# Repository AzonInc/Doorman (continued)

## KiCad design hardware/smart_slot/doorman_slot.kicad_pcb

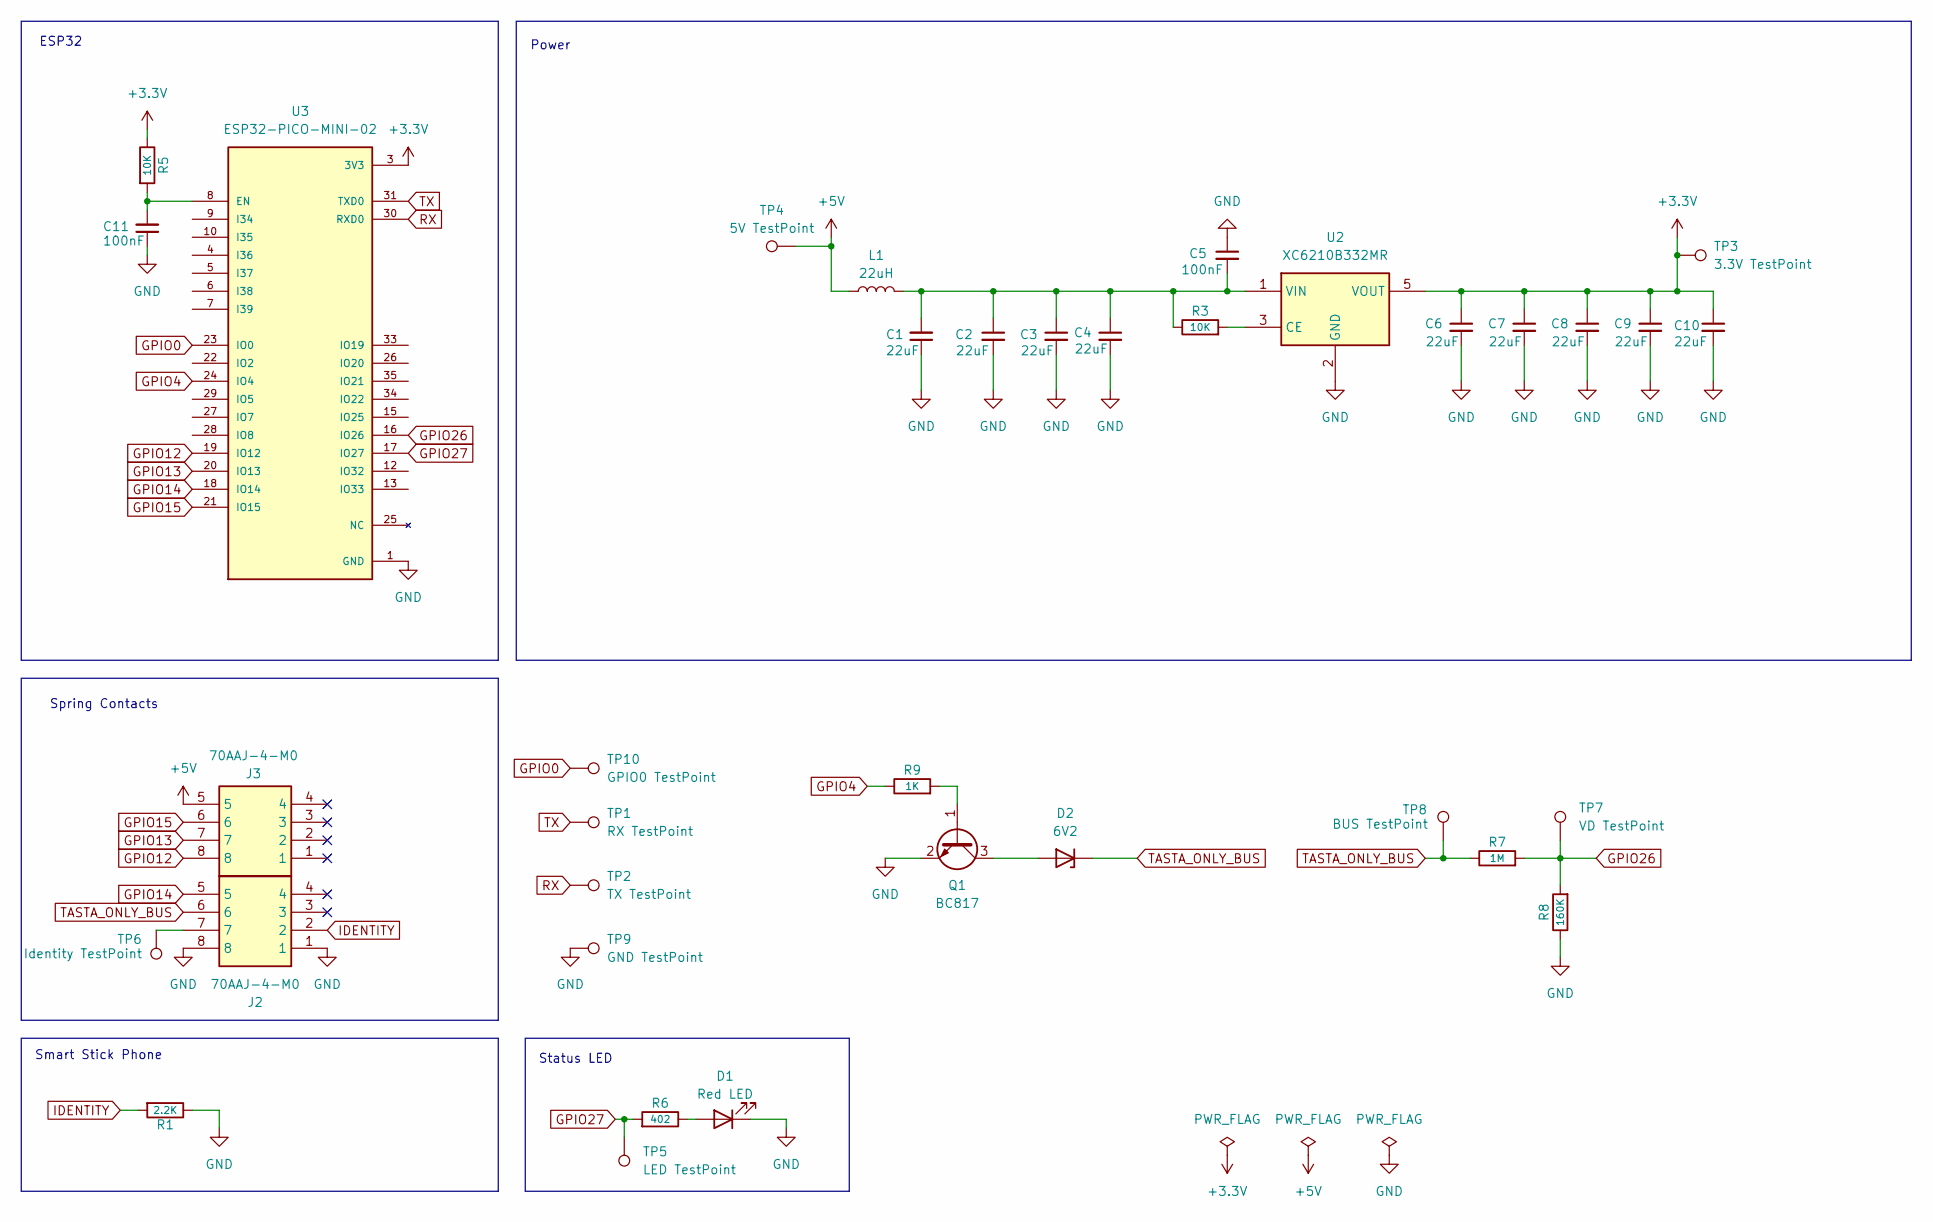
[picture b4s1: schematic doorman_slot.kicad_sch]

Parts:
C1, C2, C3, C4, C6, C7, C8, C9: 22uF; C_0603_1608Metric; LCSC C59461
C5, C11: 100nF; C_0402_1005Metric; LCSC C1525
C10: 22uF; C_0402_1005Metric; LCSC C105226
D1: Red LED; LED_0603_1608Metric
D2: 6V2; D_MiniMELF; MPN ZMM6B2; LCSC C3041470
J2, J3: 70AAJ-4-M0; 70AAJ4M0; Manufacturer_Part_Number 70AAJ-4-M0; Mouser Part Number 652-70AAJ-4-M0
L1: 22uH; L_APV_ANR4010; LCSC C83472
Q1: BC817; SOT-23; LCSC C5184412
R1: 2.2K; R_0402_1005Metric; LCSC C25879
R3, R5: 10K; R_0402_1005Metric; LCSC C25744
R6: 402; R_0402_1005Metric; LCSC C41042
R7: 1M; R_0603_1608Metric; LCSC C22935
R8: 160K; R_0603_1608Metric; LCSC C22813
R9: 1K; R_0402_1005Metric; LCSC C11702
TP1: RX TestPoint; TestPoint_Pad_D1.0mm
TP2: TX TestPoint; TestPoint_Pad_D1.0mm
TP3: 3.3V TestPoint; TestPoint_Pad_D1.0mm
TP4: 5V TestPoint; TestPoint_Pad_D1.0mm
TP5: LED TestPoint; TestPoint_Pad_D1.0mm
TP6: Identity TestPoint; TestPoint_Pad_D1.0mm
TP7: VD TestPoint; TestPoint_Pad_D1.0mm
TP8: BUS TestPoint; TestPoint_Pad_D1.0mm
TP9: GND TestPoint; TestPoint_Pad_D1.0mm
TP10: GPIO0 TestPoint; TestPoint_Pad_D1.0mm
U2: XC6210B332MR; SOT-23-5; LCSC C3021084
U3: ESP32-PICO-MINI-02; MODULE_ESP32-PICO-MINI-02; PARTREV v1.0; LCSC C2980306

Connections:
+3.3V: C6.1, C7.1, C8.1, C9.1, C10.1, R5.1, TP3.1, U2.5 (VOUT), U3.3 (3V3)
+5V: J3.5, L1.1, TP4.1
GND: C1.1, C2.2, C3.2, C4.2, C5.1, C6.2, C7.2, C8.2, C9.2, C10.2, C11.1, D1.1 (K), J2.1, J2.8, Q1.2 (E), R1.1, R8.1, TP9.1, U2.2 (GND), U3.1 (GND), U3.2 (GND), U3.11 (GND), U3.14 (GND), U3.36 (GND), U3.37 (GND), U3.38 (GND), U3.39 (GND), U3.40 (GND), U3.41 (GND), U3.42 (GND), U3.43 (GND), U3.44 (GND), U3.45 (GND), U3.46 (GND), U3.47 (GND), U3.48 (GND), U3.49 (GND), U3.50 (GND), U3.51 (GND), U3.52 (GND), U3.53 (GND), U3.54 (GND), U3.55 (GND), U3.56 (GND), U3.57 (GND), U3.58 (GND), U3.59 (GND), U3.60 (GND), U3.61 (GND)
GPIO0: TP10.1, U3.23 (IO0)
GPIO4: R9.1, U3.24 (IO4)
GPIO12: J3.8, U3.19 (IO12)
GPIO13: J3.7, U3.20 (IO13)
GPIO14: J2.5, U3.18 (IO14)
GPIO15: J3.6, U3.21 (IO15)
GPIO26: R7.2, R8.2, TP7.1, U3.16 (IO26)
GPIO27: R6.2, TP5.1, U3.17 (IO27)
IDENTITY: J2.2, R1.2
unnamed: D1.2 (A), R6.1
unnamed: D2.2 (A), Q1.3 (C)
unnamed: J2.7, TP6.1
unnamed: Q1.1 (B), R9.2
unnamed: R3.2, U2.3 (CE)
unnamed: C1.2, C2.1, C3.1, C4.1, C5.2, L1.2, R3.1, U2.1 (VIN)
unnamed: C11.2, R5.2, U3.8 (EN)
RX: TP2.1, U3.30 (RXD0)
TASTA_ONLY_BUS: D2.1 (K), J2.6, R7.1, TP8.1
TX: TP1.1, U3.31 (TXD0)

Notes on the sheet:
Spring Contacts
ESP32
Smart Stick Phone
Status LED
Power

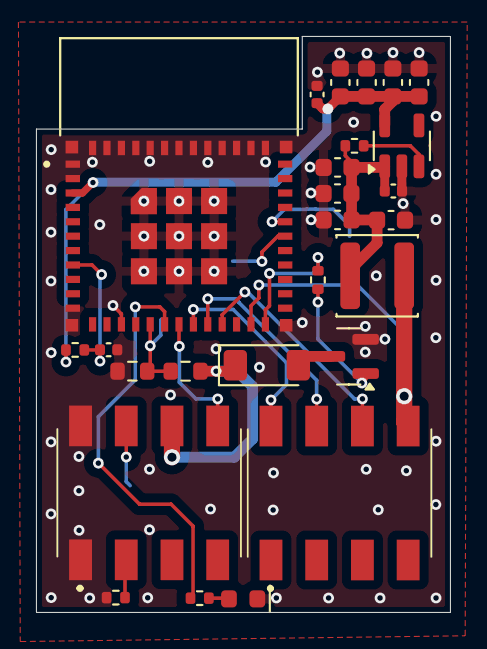
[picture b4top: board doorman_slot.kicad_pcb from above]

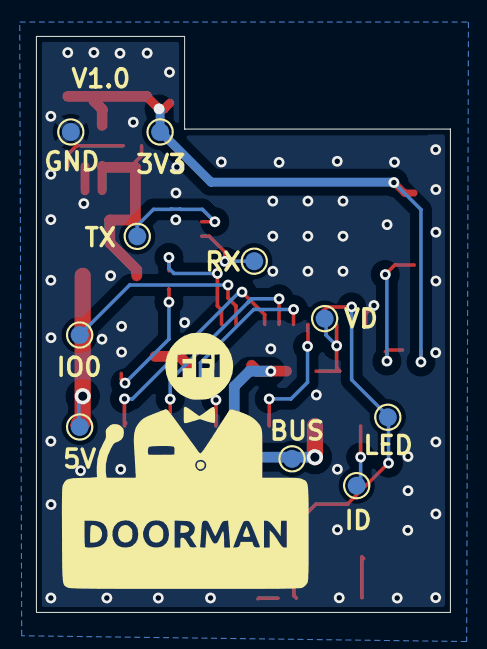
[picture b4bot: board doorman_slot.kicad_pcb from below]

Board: 4 copper layers, 23.0 x 32.0 mm, 36 parts (10 on the bottom side), 22 nets.

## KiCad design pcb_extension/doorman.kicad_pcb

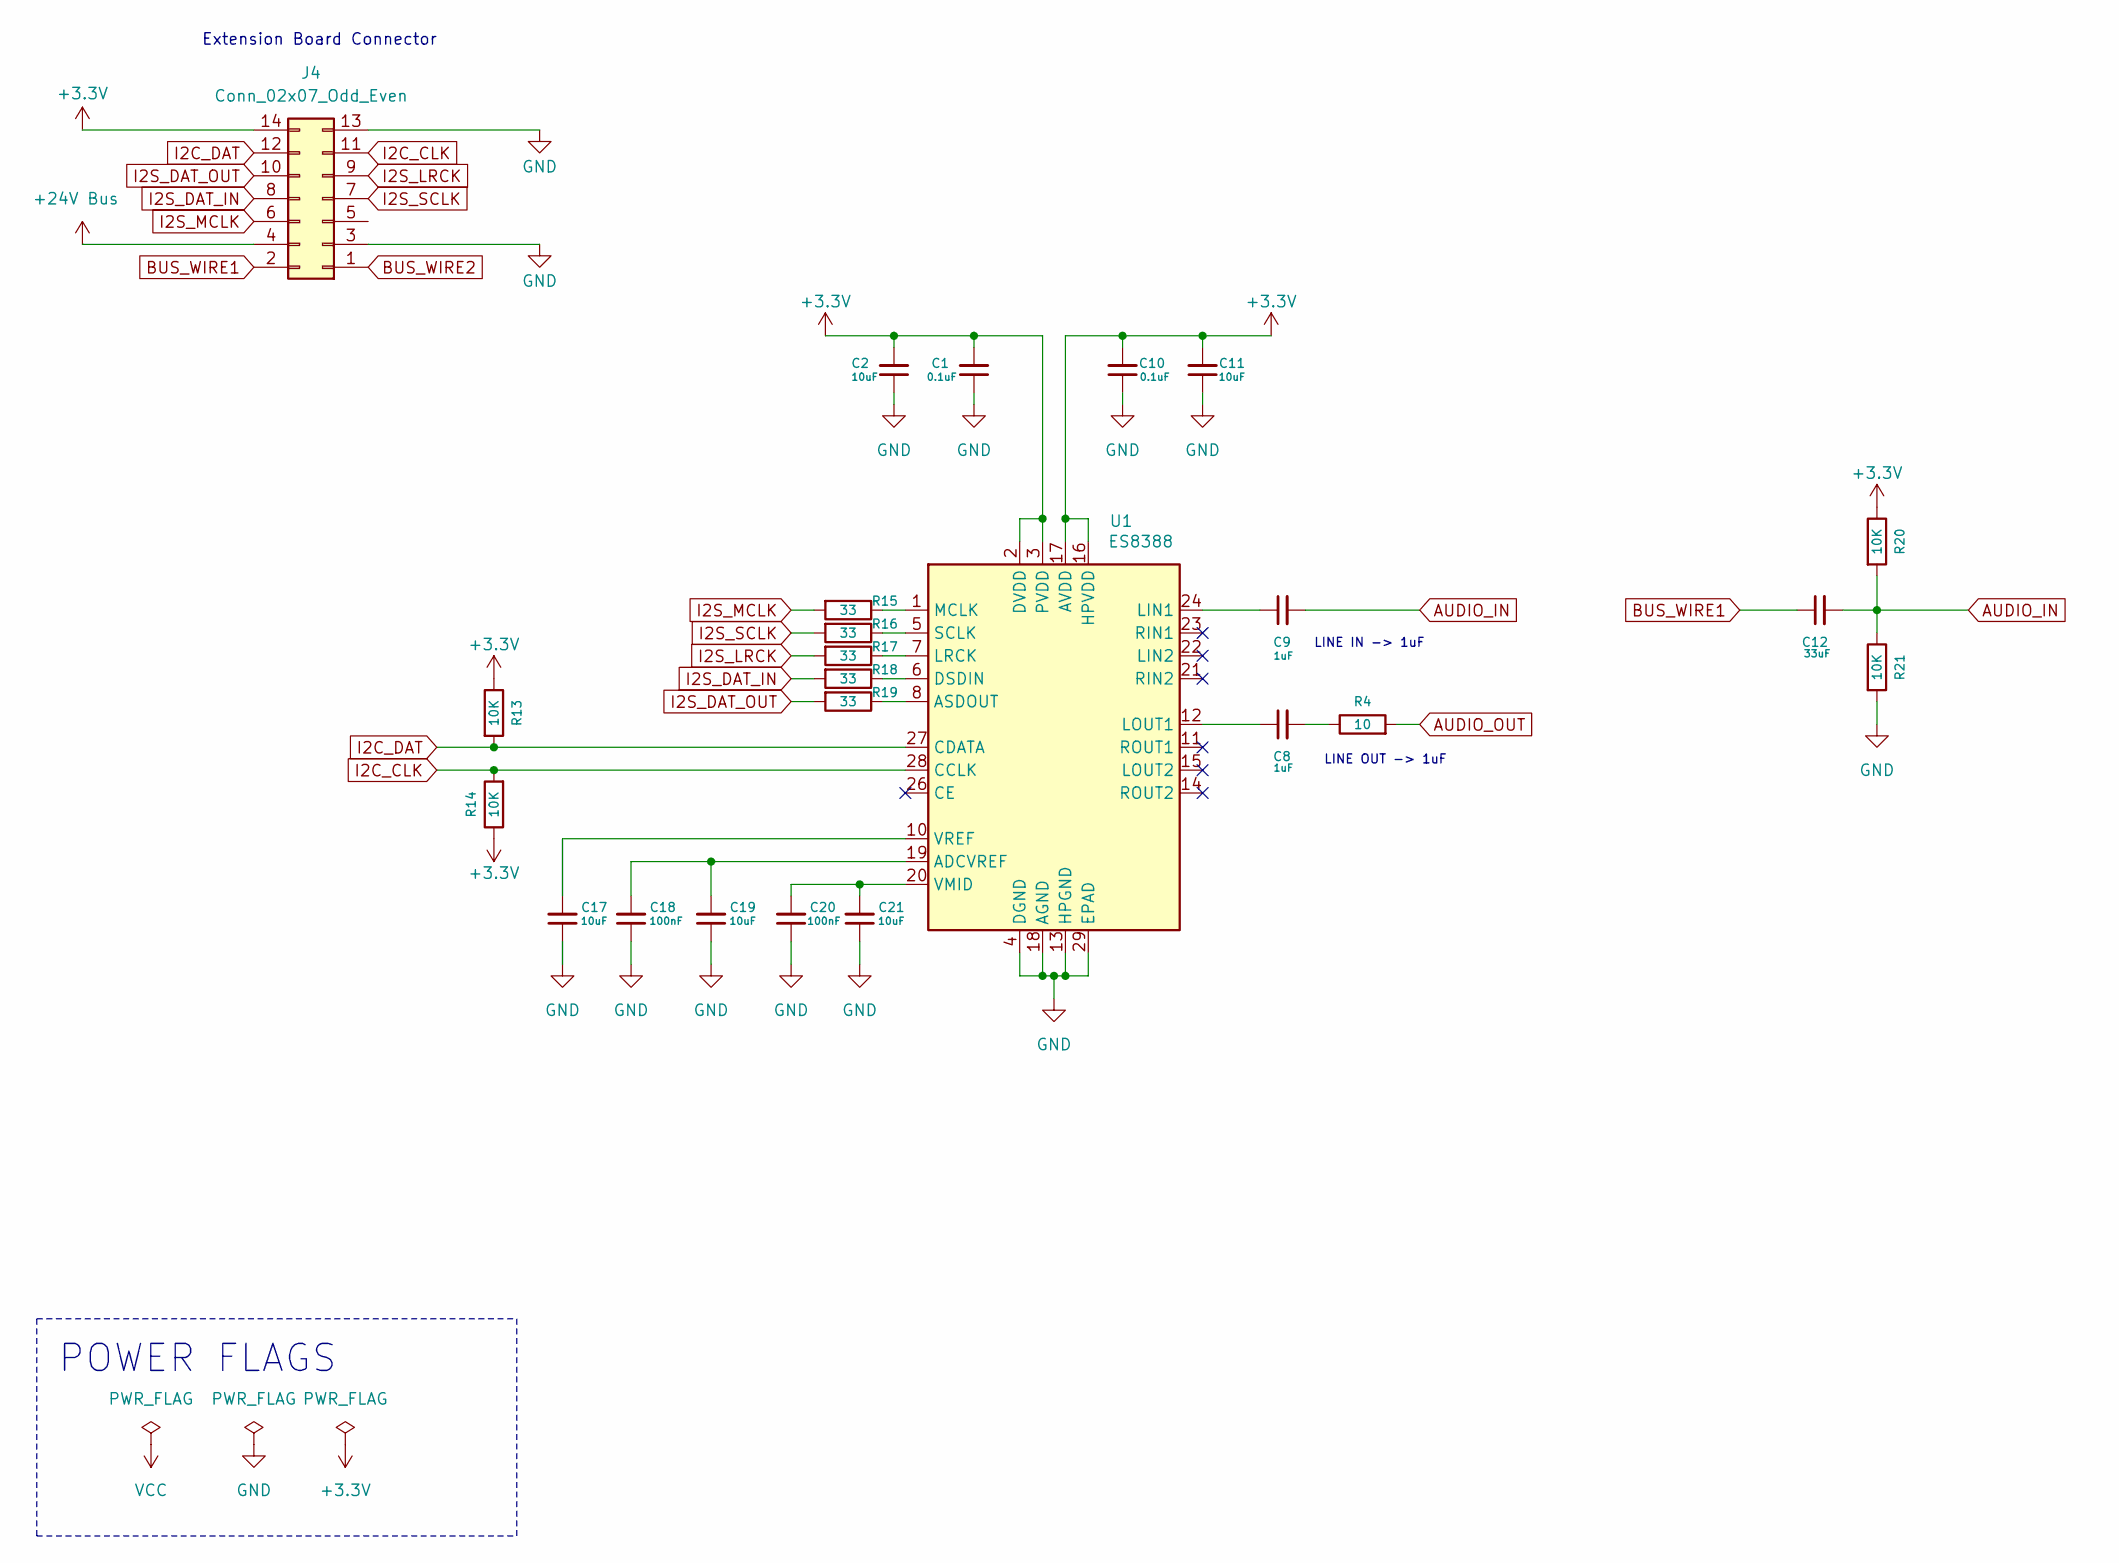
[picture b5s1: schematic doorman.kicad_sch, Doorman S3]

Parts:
C1, C10: 0.1uF; C_0603_1608Metric; MPN CC0603KRX7R9BB104; LCSC C14663
C2, C11, C17, C19, C21: 10uF; C_0603_1608Metric; MPN CC0603KRX7R9BB104; LCSC C14663
C8, C9: 1uF; C_0603_1608Metric; MPN CC0603KRX7R9BB104; LCSC C14663
C12: 33uF; C_1206_3216Metric; MPN CC0603KRX7R9BB104; LCSC C14663
C18, C20: 100nF; C_0603_1608Metric; MPN CC0603KRX7R9BB104; LCSC C14663
J4: Conn_02x07_Odd_Even; PinHeader_2x07_P2.00mm_Vertical_SMD; MPN PM200-2-07-S-4.3; LCSC C3975171
R4: 10; R_0402_1005Metric; MPN 0402WGF5101TCE; LCSC C25905
R13, R14: 10K; R_0402_1005Metric; MPN 0402WGF5101TCE; LCSC C25905
R15, R16, R17, R18, R19: 33; R_0402_1005Metric; MPN 0402WGF5101TCE; LCSC C25905
R20, R21: 10K; R_0603_1608Metric; MPN 0402WGF5101TCE; LCSC C25905
U1: ES8388; QFN-28-1EP_4x4mm_P0.45mm_EP2.6x2.6mm

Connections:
+3.3V: C1.2, C2.2, C10.2, C11.2, J4.14, R13.1, R14.1, R20.1, U1.2 (DVDD), U1.3 (PVDD), U1.16 (HPVDD), U1.17 (AVDD)
+24V Bus: J4.4
AUDIO_IN: C9.2, C12.2, R20.2, R21.1
AUDIO_OUT: R4.2
BUS_WIRE1: C12.1, J4.2
BUS_WIRE2: J4.1
GND: C1.1, C2.1, C10.1, C11.1, C17.1, C18.1, C19.1, C20.1, C21.1, J4.3, J4.13, R21.2, U1.4 (DGND), U1.13 (HPGND), U1.18 (AGND), U1.29 (EPAD)
I2C_CLK: J4.11, R14.2, U1.28 (CCLK)
I2C_DAT: J4.12, R13.2, U1.27 (CDATA)
I2S_DAT_IN: J4.8, R18.2
I2S_DAT_OUT: J4.10, R19.2
I2S_LRCK: J4.9, R17.2
I2S_MCLK: J4.6, R15.2
I2S_SCLK: J4.7, R16.2
unnamed: C8.2, R4.1
unnamed: C18.2, C19.2, U1.19 (ADCVREF)
unnamed: R19.1, U1.8 (ASDOUT)
unnamed: R18.1, U1.6 (DSDIN)
unnamed: C9.1, U1.24 (LIN1)
unnamed: C8.1, U1.12 (LOUT1)
unnamed: R17.1, U1.7 (LRCK)
unnamed: R15.1, U1.1 (MCLK)
unnamed: R16.1, U1.5 (SCLK)
unnamed: C20.2, C21.2, U1.20 (VMID)
unnamed: C17.2, U1.10 (VREF)

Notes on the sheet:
LINE OUT -> 1uF
LINE IN -> 1uF
Extension Board Connector
POWER FLAGS

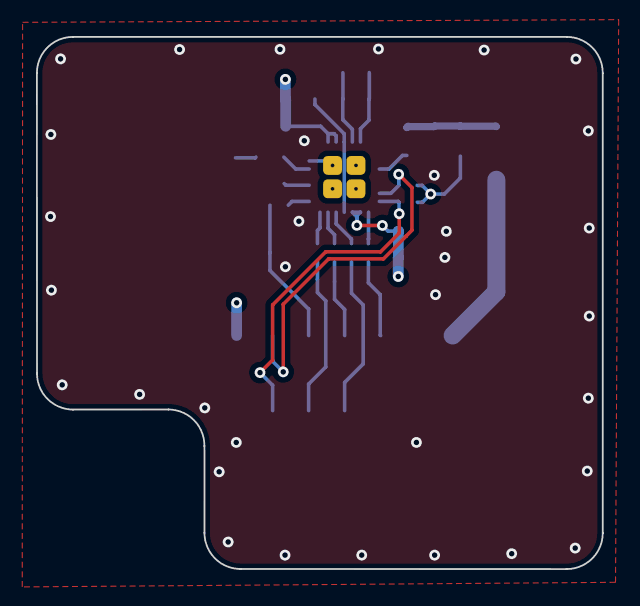
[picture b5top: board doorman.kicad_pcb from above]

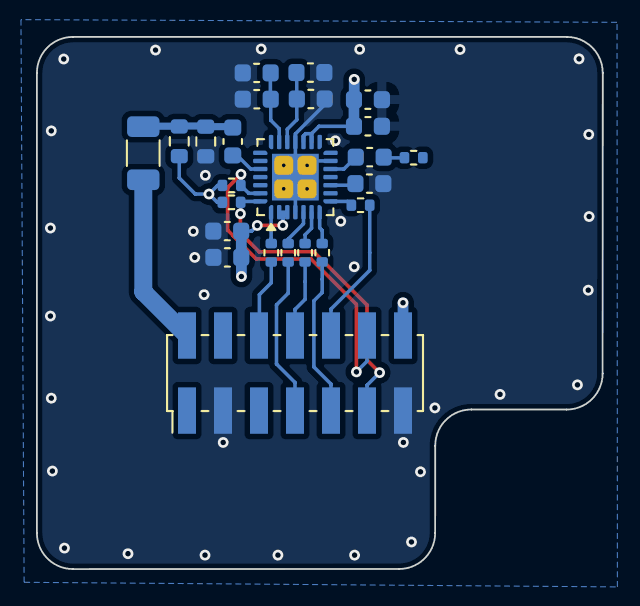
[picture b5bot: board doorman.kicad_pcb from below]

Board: 4 copper layers, 31.4 x 29.6 mm, 24 parts (24 on the bottom side), 22 nets.

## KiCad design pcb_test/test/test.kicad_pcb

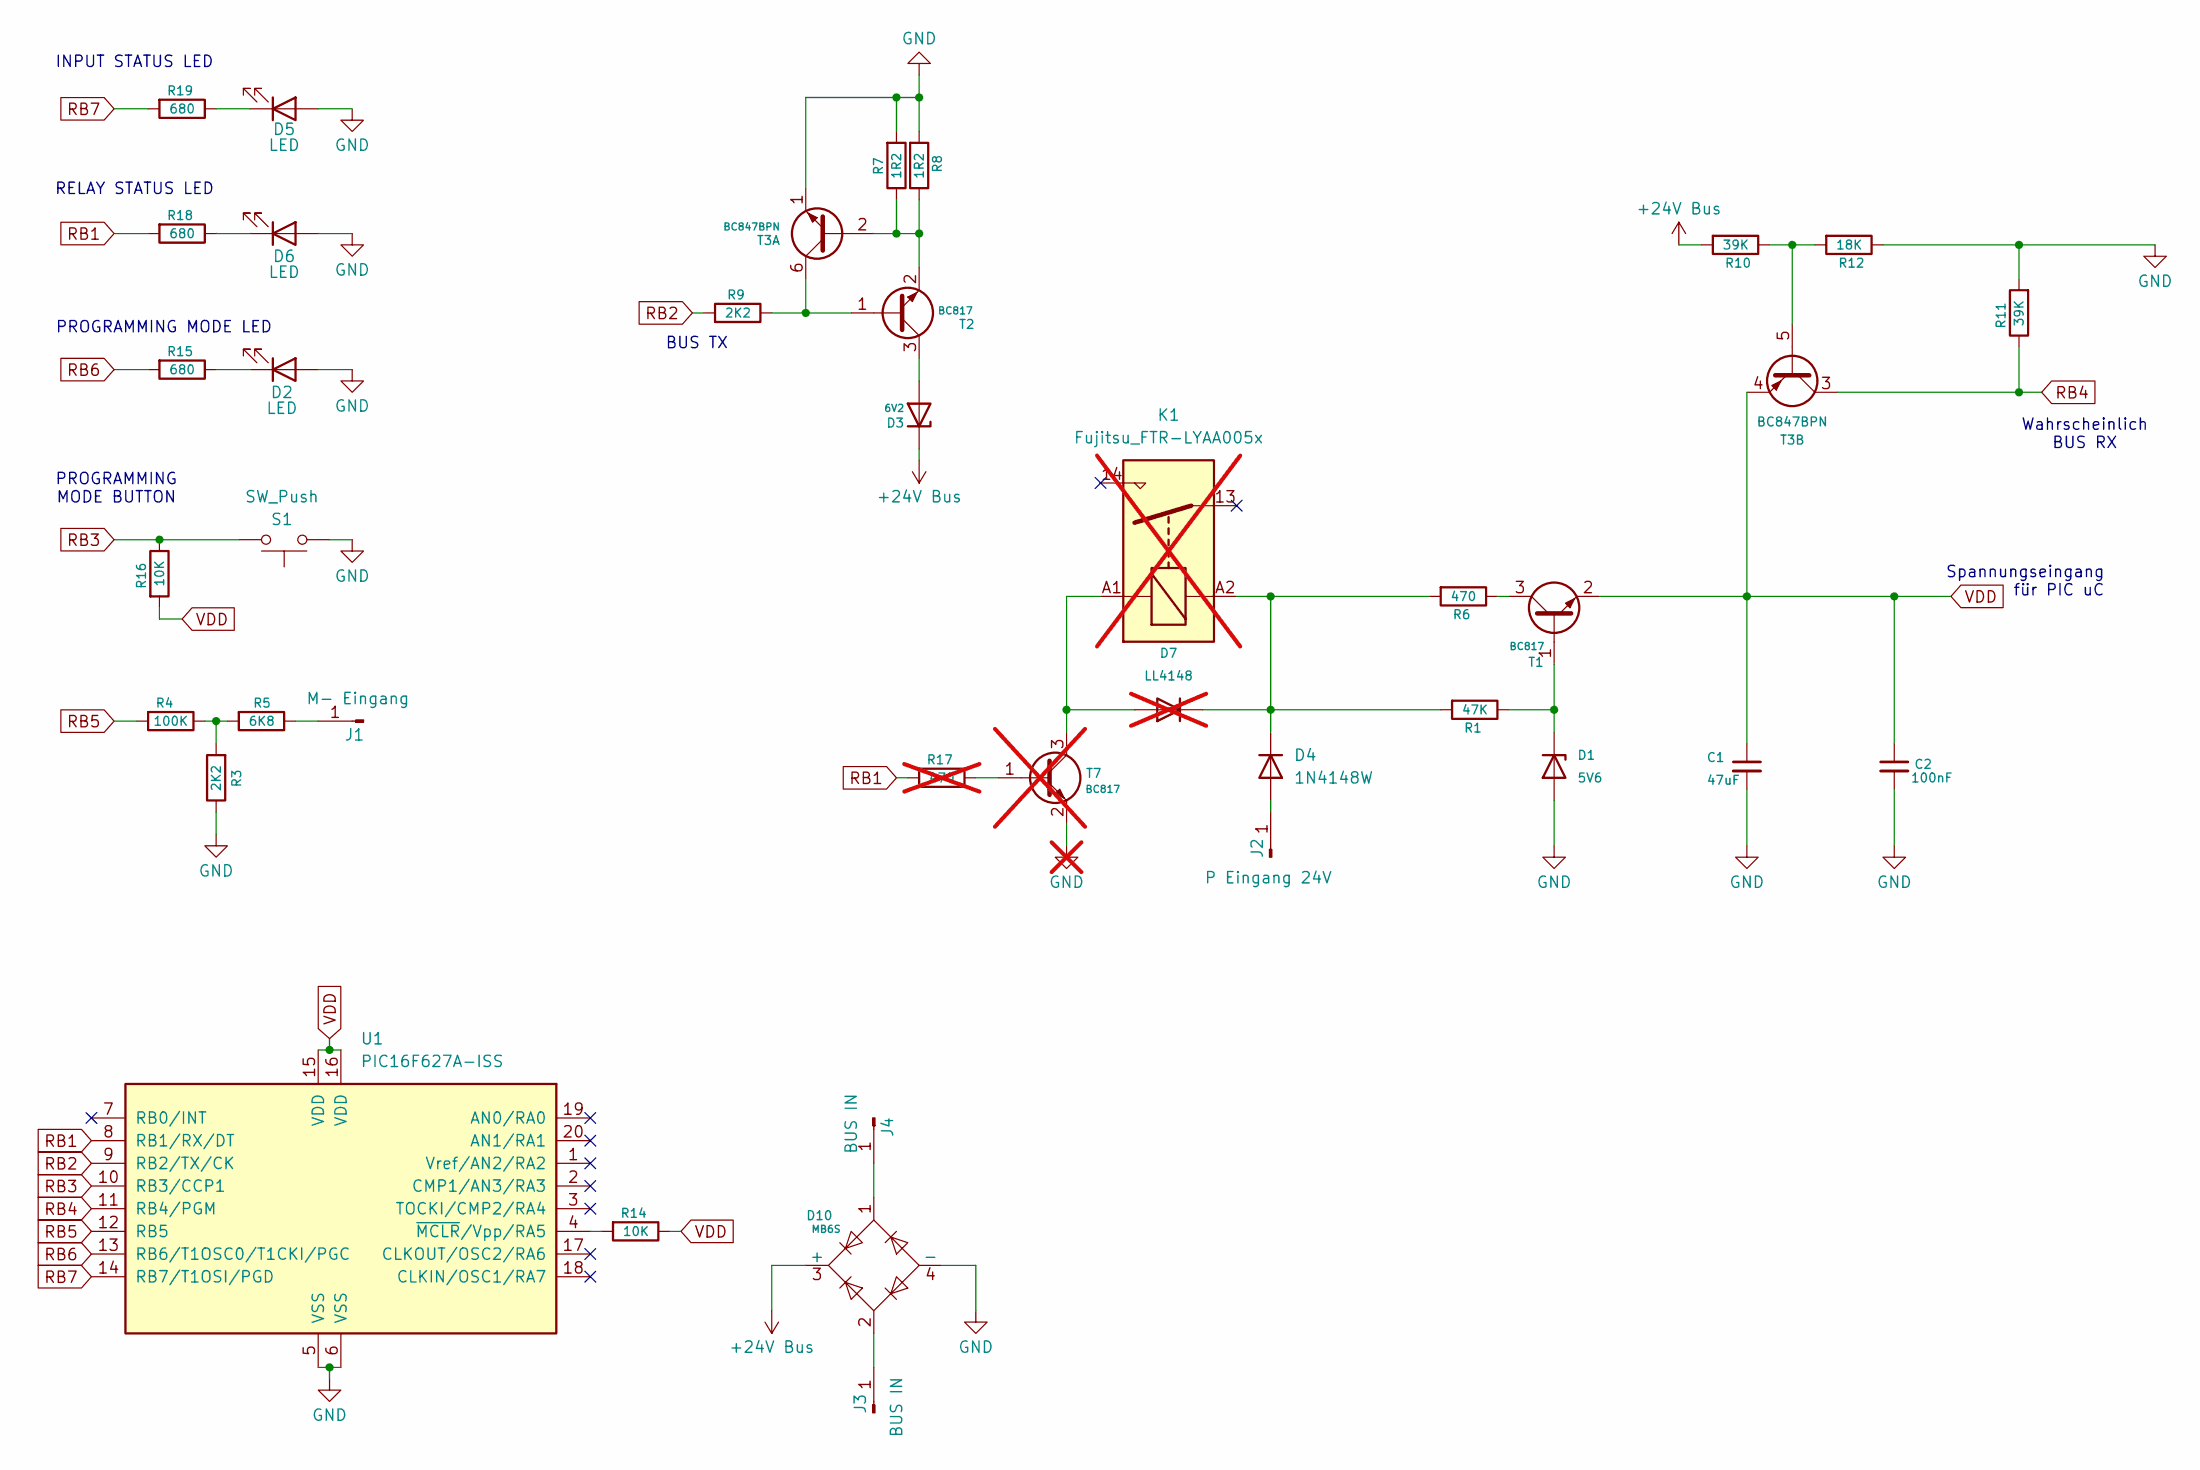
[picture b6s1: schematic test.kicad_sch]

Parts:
C1: 47uF; CP_Radial_D4.0mm_P1.50mm
C2: 100nF; C_0805_2012Metric
D1: 5V6; D_MiniMELF
D2, D5, D6: LED; LED_D3.0mm_Horizontal_O1.27mm_Z2.0mm
D3: 6V2; D_MELF
D4: 1N4148W; D_SOD-123
D7: LL4148; D_MiniMELF; not fitted
D10: MB6S; TO-269AA; MPN MB6S; LCSC C2886734
J1: M- Eingang; PinHeader_1x01_P2.54mm_Vertical
J2: P Eingang 24V; PinHeader_1x01_P2.54mm_Vertical
J3, J4: BUS IN; PinHeader_1x01_P2.54mm_Vertical
K1: Fujitsu_FTR-LYAA005x; Relay_SPST-NO_Fujitsu_FTR-LYAA005x_FormA_Vertical; not fitted
R1: 47K; R_0805_2012Metric
R3, R9: 2K2; R_0805_2012Metric
R4: 100K; R_0805_2012Metric
R5: 6K8; R_0805_2012Metric
R6: 470; R_0805_2012Metric
R7, R8: 1R2; R_0805_2012Metric
R10, R11: 39K; R_0805_2012Metric
R12: 18K; R_0805_2012Metric
R14, R16: 10K; R_0805_2012Metric
R15, R18, R19: 680; R_0805_2012Metric
R17: 470; R_0805_2012Metric; not fitted
S1: SW_Push; SW_Tactile_SPST_Angled_PTS645Vx31-2LFS
T1, T2: BC817; SOT-23; MPN BC817-25; LCSC C5184412
T3: BC847BPN; SOT-363_SC-70-6
T7: BC817; SOT-23; MPN BC817-25; LCSC C5184412; not fitted
U1: PIC16F627A-ISS; SSOP-20_4.4x6.5mm_P0.65mm

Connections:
+24V Bus: D3.1 (K), D10.3 (+), R10.2
GND: C1.2, C2.2, D1.2 (A), D2.2 (A), D5.2 (A), D6.2 (A), D10.4 (-), R3.1, R7.2, R8.2, R11.2, R12.1, S1.2, T3.1 (E1), T7.2 (E), U1.5 (VSS), U1.6 (VSS)
unnamed: D1.1 (K), R1.1, T1.1 (B)
unnamed: D2.1 (K), R15.1
unnamed: D3.2 (A), T2.3 (C)
unnamed: D4.2 (A), J2.1
unnamed: D4.1 (K), D7.1 (K), K1.A2, R1.2, R6.2
unnamed: D5.1 (K), R19.1
unnamed: D6.1 (K), R18.1
unnamed: D7.2 (A), K1.A1, T7.3 (C)
unnamed: J1.1, R5.1
unnamed: D10.2, J3.1
unnamed: D10.1, J4.1
unnamed: R3.2, R4.1, R5.2
unnamed: R6.1, T1.3 (C)
unnamed: R9.1, T2.1 (B), T3.6 (C1)
unnamed: R7.1, R8.1, T2.2 (E), T3.2 (B1)
unnamed: R10.1, R12.2, T3.5 (B2)
unnamed: R17.1, T7.1 (B)
unnamed: R14.2, U1.4 (~MCLR/Vpp/RA5)
RB1: R17.2, R18.2, U1.8 (RB1/RX/DT)
RB2: R9.2, U1.9 (RB2/TX/CK)
RB3: R16.1, S1.1, U1.10 (RB3/CCP1)
RB4: R11.1, T3.3 (C2), U1.11 (RB4/PGM)
RB5: R4.2, U1.12 (RB5)
RB6: R15.2, U1.13 (RB6/T1OSC0/T1CKI/PGC)
RB7: R19.2, U1.14 (RB7/T1OSI/PGD)
VDD: C1.1, C2.1, R14.1, R16.2, T1.2 (E), T3.4 (E2), U1.15 (VDD), U1.16 (VDD)

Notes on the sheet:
Wahrscheinlich BUS RX
Spannungseingang für PIC uC
INPUT STATUS LED
PROGRAMMING MODE BUTTON
RELAY STATUS LED
PROGRAMMING MODE LED
BUS TX

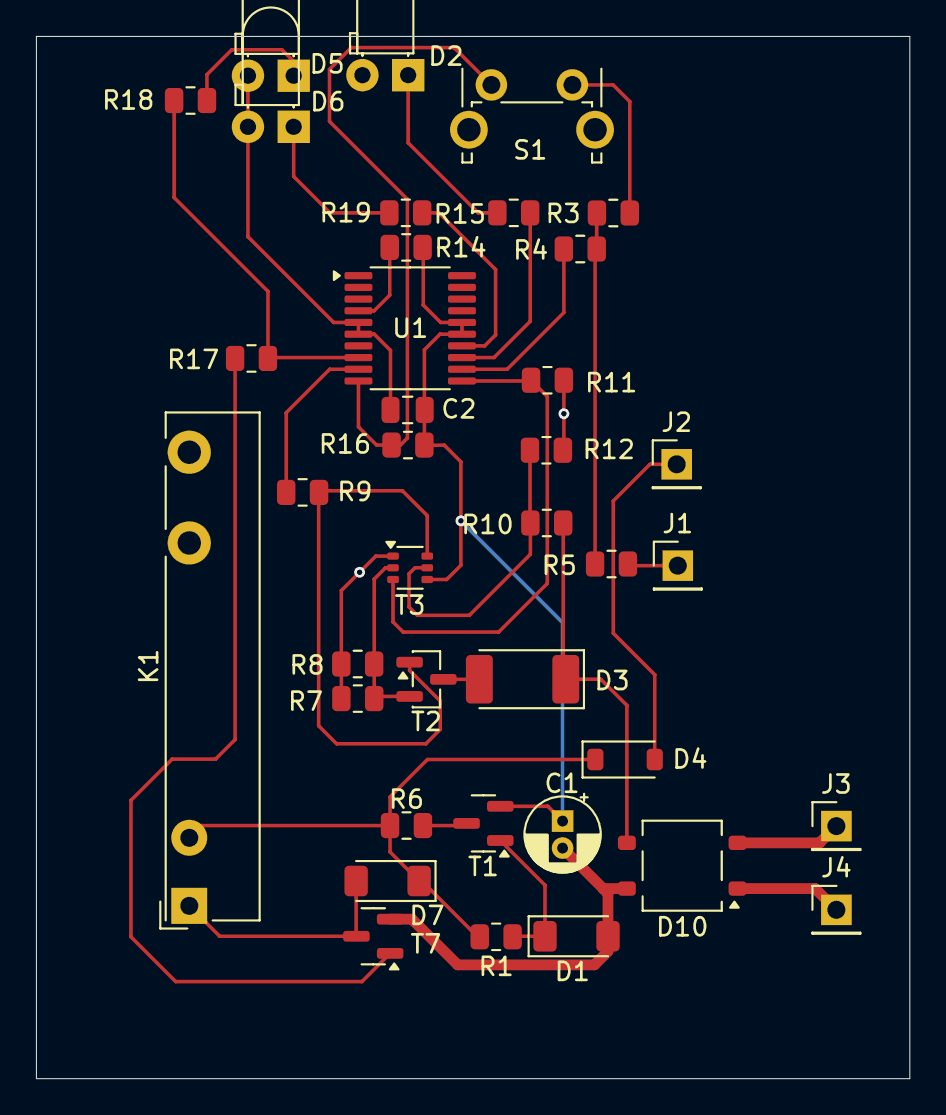
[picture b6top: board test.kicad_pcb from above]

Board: 2 copper layers, 48.5 x 57.9 mm, 38 parts (0 on the bottom side), 28 nets.

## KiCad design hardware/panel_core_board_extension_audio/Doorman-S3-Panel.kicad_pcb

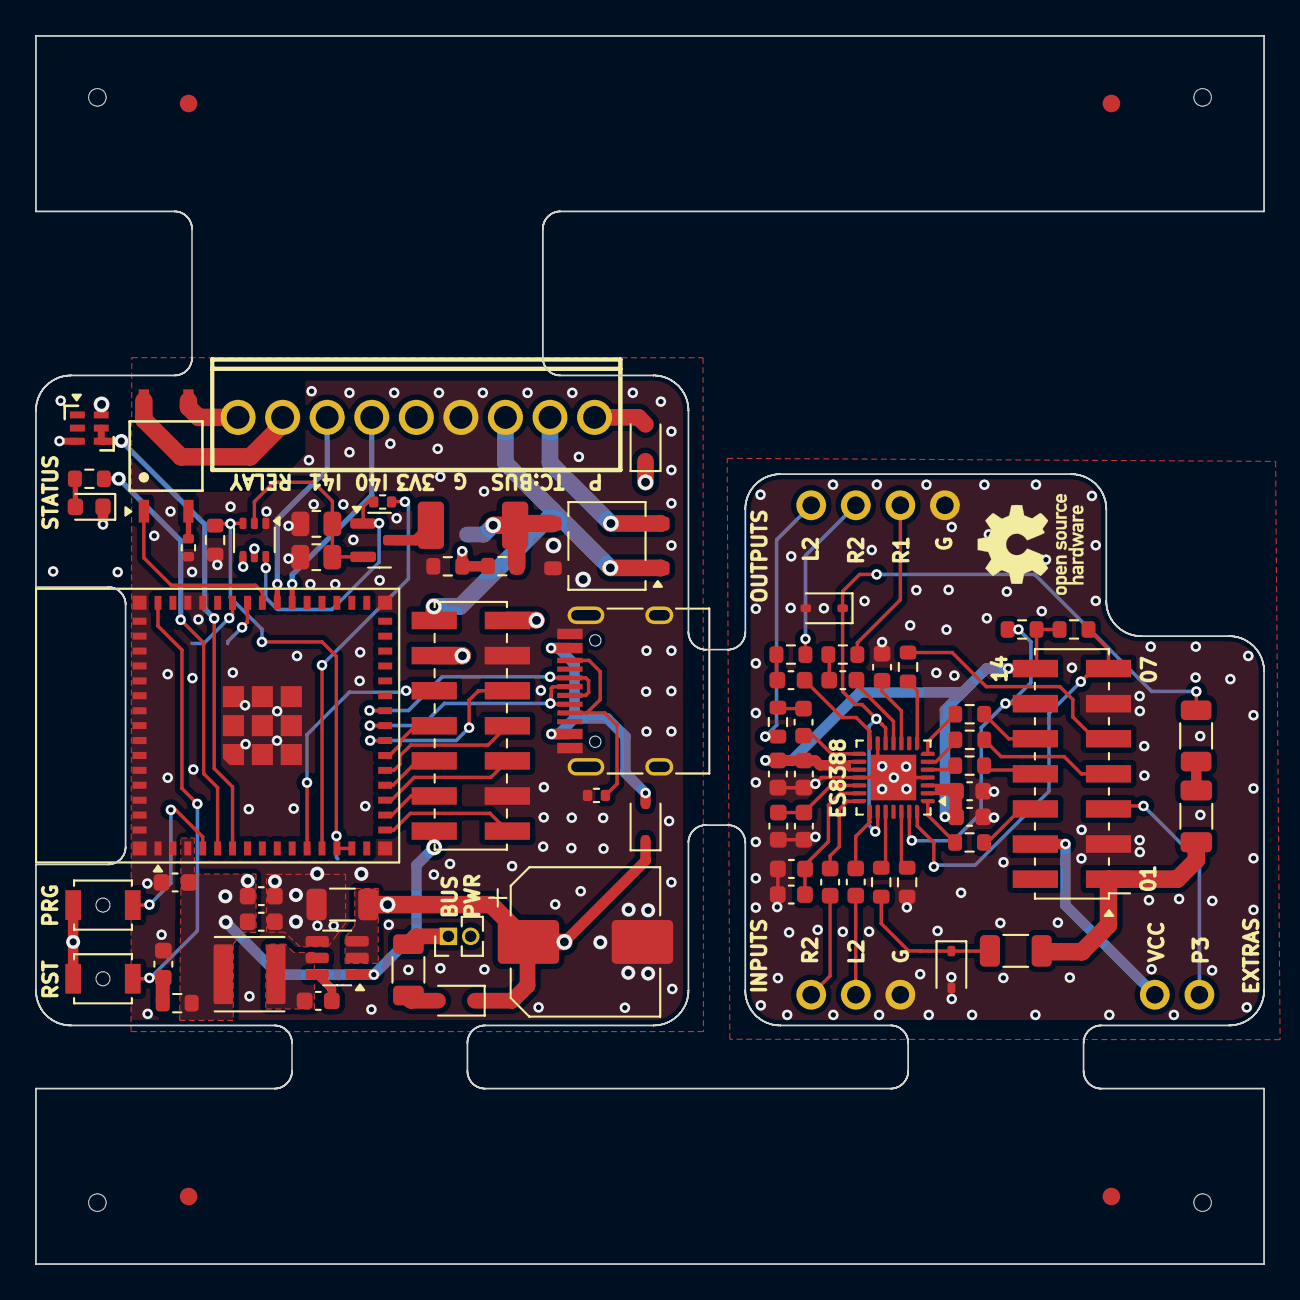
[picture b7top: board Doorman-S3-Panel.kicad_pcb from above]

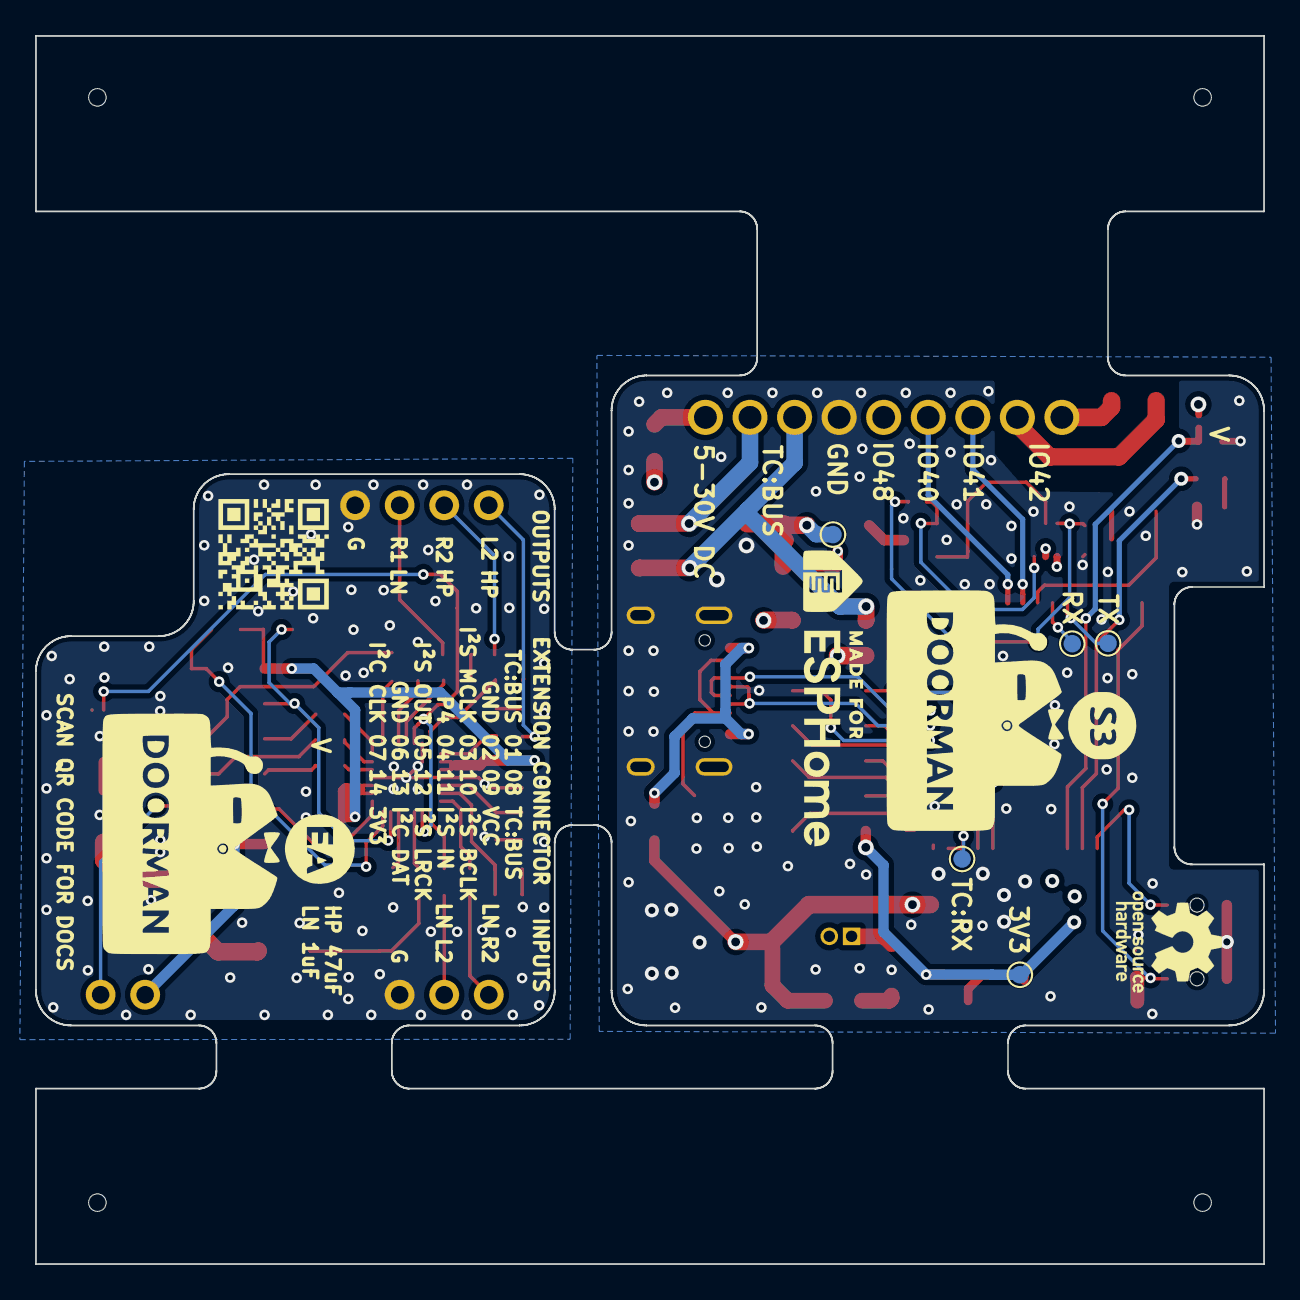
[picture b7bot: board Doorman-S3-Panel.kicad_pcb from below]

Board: 4 copper layers, 70.0 x 70.0 mm, 84 parts (12 on the bottom side), 80 nets.

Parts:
B0-C1, B0-C2, B0-C5, B1-C1, B1-C10, B1-C18, B1-C20: 100nF; C_0603_1608Metric
B0-C3: 470uF; CP_Elec_8x10
B0-C4, B1-C12, B1-C14: 10uF; C_1206_3216Metric
B0-C6, B0-C7: 22uF; C_0603_1608Metric
B0-D1, B0-D5, B0-D6: 1N5819WS; D_SOD-323
B0-D2: MB6S; TO-269AA
B0-D4: Red; LED_0603_1608Metric
B0-D7: 6.2V; D_MELF
B0-D8: XL-2020RGBC-SK6812B; LED-SMD_6P-L2.0-W2.0_XL-2020RGBC
B0-G***: LOGO; esphome
B0-G***#2, B1-G***: LOGO; doorman-s3-2
B0-J1: USB-C Connector; USB_C_Receptacle_HRO_TYPE-C-31-M-12
B0-J2: Screw Terminals; CONN-TH_9P-P2.54_KF128-2.54-9P
B0-J3: 3V3 Test Pad; TestPoint_Pad_D1.0mm
B0-J4: Extension Board Connector; PinSocket_2x07_P2.00mm_Vertical_SMD
B0-J6: BUS Test Pad; TestPoint_Pad_D1.0mm
B0-J7: BUS RX Test Pad; TestPoint_Pad_D1.0mm
B0-J8: TX Test Pad; TestPoint_Pad_D1.0mm
B0-J9: RX Test Pad; TestPoint_Pad_D1.0mm
B0-JP1: Bus power Jumper; PinHeader_1x02_P1.27mm_Vertical
B0-L1: 3.9uH; L_Abracon_ASPI-4030S
B0-Q1: BC847BPN; SOT-363_SC-70-6
B0-Q2: BC817; SOT-23
B0-R1, B0-R6, B1-R5, B1-R13, B1-R14: 10K; R_0603_1608Metric
B0-R2: 2K2; R_0402_1005Metric
B0-R3: 5K1; R_0402_1005Metric
B0-R5, B0-R12: 47K5; R_0603_1608Metric
B0-R7: 470R; R_0603_1608Metric
B0-R8, B0-R11: 1R2; R_0805_2012Metric
B0-R9: 150R; R_0402_1005Metric
B0-R10: 62R; R_1206_3216Metric
B0-REF**, B1-REF**: OSHW-Logo_5.7x6mm_SilkScreen
B0-SW1, B0-SW2: Button; SW_SPST_B3U-1000P-B
B0-U2: AP63203WU; TSOT-23-6
B0-U3: GAQY252G3S; SOP-4_L4.4-W4.0-P2.54-LS7.0-TL
B0-U4: ESP32-S3-MINI-1; ESP32-S2-MINI-1
B1-C2, B1-C11, B1-C17, B1-C19, B1-C21: 10uF; C_0603_1608Metric
B1-C3, B1-C5, B1-C6: 1uF; C_0603_1608Metric
B1-C7, B1-C13: 47uF; C_0603_1608Metric
B1-D1, B1-D2: CDSOD323-T03S; D_SOD-323
B1-G***#2: LOGO; doorman-web-qr
B1-J1: Audio Out; PinHeader_1x04_P2.54mm_Vertical
B1-J2: GPIO; PinHeader_1x02_P2.54mm_Vertical
B1-J4: Extension Board Connector; PinHeader_2x07_P2.00mm_Vertical_SMD
B1-J5: Audio In; PinHeader_1x03_P2.54mm_Vertical
B1-R1, B1-R2, B1-R3: 10; R_0603_1608Metric
B1-R4: 0; R_0603_1608Metric
B1-R6: 200; R_1206_3216Metric
B1-R15, B1-R16, B1-R17, B1-R18, B1-R19: 33; R_0603_1608Metric
B1-U1: ES8388; QFN-28-1EP_4x4mm_P0.45mm_EP2.6x2.6mm

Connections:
B0-+3.3V: B0-C2.2, B0-C6.1, B0-C7.1, B0-D8.6 (VDD), B0-J2.5, B0-J3.1, B0-J4.2, B0-L1.2, B0-Q1.4 (E2), B0-R1.1, B0-U2.1 (FB), B0-U4.3 (3V3)
B0-+5V: B0-D1.2 (A), B0-J1.A4 (VBUS), B0-J1.A9 (VBUS), B0-J1.B4 (VBUS), B0-J1.B9 (VBUS)
B0-+24V Bus: B0-D2.3 (+), B0-D7.1 (K), B0-J6.1, B0-JP1.2 (B), B0-R5.2
B0-/EN: B0-C1.1, B0-R1.2, B0-SW1.1, B0-U4.45 (EN)
B0-/FLASH: B0-SW2.1, B0-U4.4 (IO0)
B0-/RXD: B0-J9.1, B0-U4.40 (RXD0)
B0-/TXD: B0-J8.1, B0-U4.39 (TXD0)
B0-/VCC_IN: B0-C3.1, B0-C4.1, B0-D1.1 (K), B0-D5.1 (K), B0-D6.1 (K), B0-J4.12, B0-U2.2 (EN), B0-U2.3 (IN)
B0-BUS_RX: B0-J7.1, B0-Q1.3 (C2), B0-R12.1, B0-U4.13 (IO9), B0-U4.14 (IO10)
B0-BUS_TX: B0-R2.1, B0-U4.12 (IO8)
B0-BUS_WIRE1: B0-D2.1, B0-J2.3, B0-J4.14
B0-BUS_WIRE2: B0-D2.2, B0-J2.2, B0-J4.13
B0-GND: B0-C1.2, B0-C2.1, B0-C3.2, B0-C4.2, B0-C6.2, B0-C7.2, B0-D2.4 (-), B0-D4.1 (K), B0-D8.3 (GND), B0-J1.A1 (GND), B0-J1.A12 (GND), B0-J1.B1 (GND), B0-J1.B12 (GND), B0-J1.S1 (SHIELD), B0-J2.4, B0-J4.3, B0-J4.11, B0-Q1.1 (E1), B0-R3.2, B0-R6.2, B0-R8.2, B0-R9.2, B0-R11.2, B0-R12.2, B0-SW1.2, B0-SW2.2, B0-U2.4 (GND), B0-U4.1 (GND), B0-U4.2 (GND), B0-U4.42 (GND), B0-U4.43 (GND), B0-U4.46 (GND), B0-U4.47 (GND), B0-U4.48 (GND), B0-U4.49 (GND), B0-U4.50 (GND), B0-U4.51 (GND), B0-U4.52 (GND), B0-U4.53 (GND), B0-U4.54 (GND), B0-U4.55 (GND), B0-U4.56 (GND), B0-U4.57 (GND), B0-U4.58 (GND), B0-U4.59 (GND), B0-U4.60 (GND), B0-U4.61 (GND), B0-U4.62 (GND), B0-U4.63 (GND), B0-U4.64 (GND), B0-U4.65 (GND)
B0-I2C_CLK: B0-J4.1, B0-U4.16 (IO12)
B0-I2C_DAT: B0-J4.4, B0-U4.17 (IO13)
B0-IO7: B0-J4.10, B0-U4.11 (IO7)
B0-IO14: B0-J4.5, B0-U4.18 (IO14)
B0-IO15: B0-J4.6, B0-U4.19 (IO15)
B0-IO16: B0-J4.7, B0-U4.20 (IO16)
B0-IO17: B0-J4.8, B0-U4.21 (IO17)
B0-IO18: B0-J4.9, B0-U4.22 (IO18)
B0-IO40: B0-J2.6, B0-U4.36 (IO40)
B0-IO41: B0-J2.7, B0-U4.37 (IO41)
B0-LED_RED: B0-R7.1, B0-U4.5 (IO1)
B0-LED_RGB: B0-D8.4 (DI2), B0-D8.5 (DI1), B0-U4.6 (IO2)
B0-Net-(D4-A): B0-D4.2 (A), B0-R7.2
B0-Net-(D6-A): B0-D6.2 (A), B0-R10.1
B0-Net-(D7-A): B0-D7.2 (A), B0-Q2.3 (C)
B0-Net-(J1-CC1): B0-J1.A5 (CC1), B0-J1.B5 (CC2), B0-R3.1
B0-Net-(JP1-A): B0-JP1.1 (A), B0-R10.2
B0-Net-(Q1A-B1): B0-Q1.2 (B1), B0-Q2.2 (E), B0-R8.1, B0-R11.1
B0-Net-(Q1A-C1): B0-Q1.6 (C1), B0-Q2.1 (B), B0-R2.2
B0-Net-(Q1B-B2): B0-Q1.5 (B2), B0-R5.1, B0-R6.1
B0-Net-(R9-Pad1): B0-R9.1, B0-U3.2
B0-Net-(U2-BST): B0-C5.1, B0-U2.6 (BST)
B0-Net-(U2-SW): B0-C5.2, B0-L1.1, B0-U2.5 (SW)
B0-RELAY_WIRE1: B0-J2.9, B0-U3.3
B0-RELAY_WIRE2: B0-J2.8, B0-U3.4
B0-SSR: B0-U3.1, B0-U4.38 (IO42)
B0-USB_D+: B0-J1.A6 (D+), B0-J1.B6 (D+), B0-U4.24 (USB_D+)
B0-USB_D-: B0-J1.A7 (D-), B0-J1.B7 (D-), B0-U4.23 (USB_D-)
B0-VCC: B0-D5.2 (A), B0-J2.1
B1-+3.3V: B1-C1.2, B1-C2.2, B1-C10.2, B1-C11.2, B1-J4.14, B1-R13.1, B1-R14.1, B1-U1.2 (DVDD), B1-U1.3 (PVDD), B1-U1.16 (HPVDD), B1-U1.17 (AVDD)
B1-AUDIO_IN_L1: B1-R4.1, B1-U1.24 (LIN1)
B1-AUDIO_IN_L2: B1-C5.2, B1-J5.2
B1-AUDIO_IN_R2: B1-C3.2, B1-J5.1
B1-AUDIO_OUT_L1: B1-D2.1 (K), B1-R6.1, B1-U1.12 (LOUT1), B1-U1.23 (RIN1)
B1-AUDIO_OUT_L2: B1-J1.1, B1-R2.2
B1-AUDIO_OUT_R1: B1-J1.3, B1-R1.2
B1-AUDIO_OUT_R2: B1-J1.2, B1-R3.2
B1-BUS_WIRE2: B1-C12.1, B1-C14.1, B1-J4.1
B1-GND: B1-C1.1, B1-C2.1, B1-C10.1, B1-C11.1, B1-C17.1, B1-C18.1, B1-C19.1, B1-C20.1, B1-C21.1, B1-D1.2 (A), B1-D2.2 (A), B1-J1.4, B1-J4.2, B1-J4.6, B1-J5.3, B1-R5.1, B1-U1.4 (DGND), B1-U1.13 (HPGND), B1-U1.18 (AGND), B1-U1.29 (EPAD)
B1-I2C_CLK: B1-J4.7, B1-R14.2, B1-U1.28 (CCLK)
B1-I2C_DAT: B1-J4.13, B1-R13.2, B1-U1.27 (CDATA)
B1-I2S_BCLK: B1-J4.11, B1-R16.2
B1-I2S_DAT_IN: B1-J4.4, B1-R18.2
B1-I2S_DAT_OUT: B1-J4.5, B1-R19.2
B1-I2S_LRCK: B1-J4.12, B1-R17.2
B1-I2S_MCLK: B1-J4.10, B1-R15.2
B1-Net-(C6-Pad2): B1-C6.2, B1-R1.1
B1-Net-(C7-Pad2): B1-C7.2, B1-R2.1
B1-Net-(C13-Pad2): B1-C13.2, B1-R3.1
B1-Net-(C14-Pad2): B1-C14.2, B1-R6.2
B1-Net-(D1-K): B1-C12.2, B1-D1.1 (K), B1-R4.2
B1-Net-(U1-ADCVREF): B1-C18.2, B1-C19.2, B1-U1.19 (ADCVREF)
B1-Net-(U1-ASDOUT): B1-R19.1, B1-U1.8 (ASDOUT)
B1-Net-(U1-CE): B1-R5.2, B1-U1.26 (CE)
B1-Net-(U1-DSDIN): B1-R18.1, B1-U1.6 (DSDIN)
B1-Net-(U1-LIN2): B1-C5.1, B1-U1.22 (LIN2)
B1-Net-(U1-LOUT2): B1-C7.1, B1-U1.15 (LOUT2)
B1-Net-(U1-LRCK): B1-R17.1, B1-U1.7 (LRCK)
B1-Net-(U1-MCLK): B1-R15.1, B1-U1.1 (MCLK)
B1-Net-(U1-RIN2): B1-C3.1, B1-U1.21 (RIN2)
B1-Net-(U1-ROUT1): B1-C6.1, B1-U1.11 (ROUT1)
B1-Net-(U1-ROUT2): B1-C13.1, B1-U1.14 (ROUT2)
B1-Net-(U1-SCLK): B1-R16.1, B1-U1.5 (SCLK)
B1-Net-(U1-VMID): B1-C20.2, B1-C21.2, B1-U1.20 (VMID)
B1-Net-(U1-VREF): B1-C17.2, B1-U1.10 (VREF)
B1-PIN3: B1-J2.1, B1-J4.3
B1-VCC: B1-J2.2, B1-J4.9
